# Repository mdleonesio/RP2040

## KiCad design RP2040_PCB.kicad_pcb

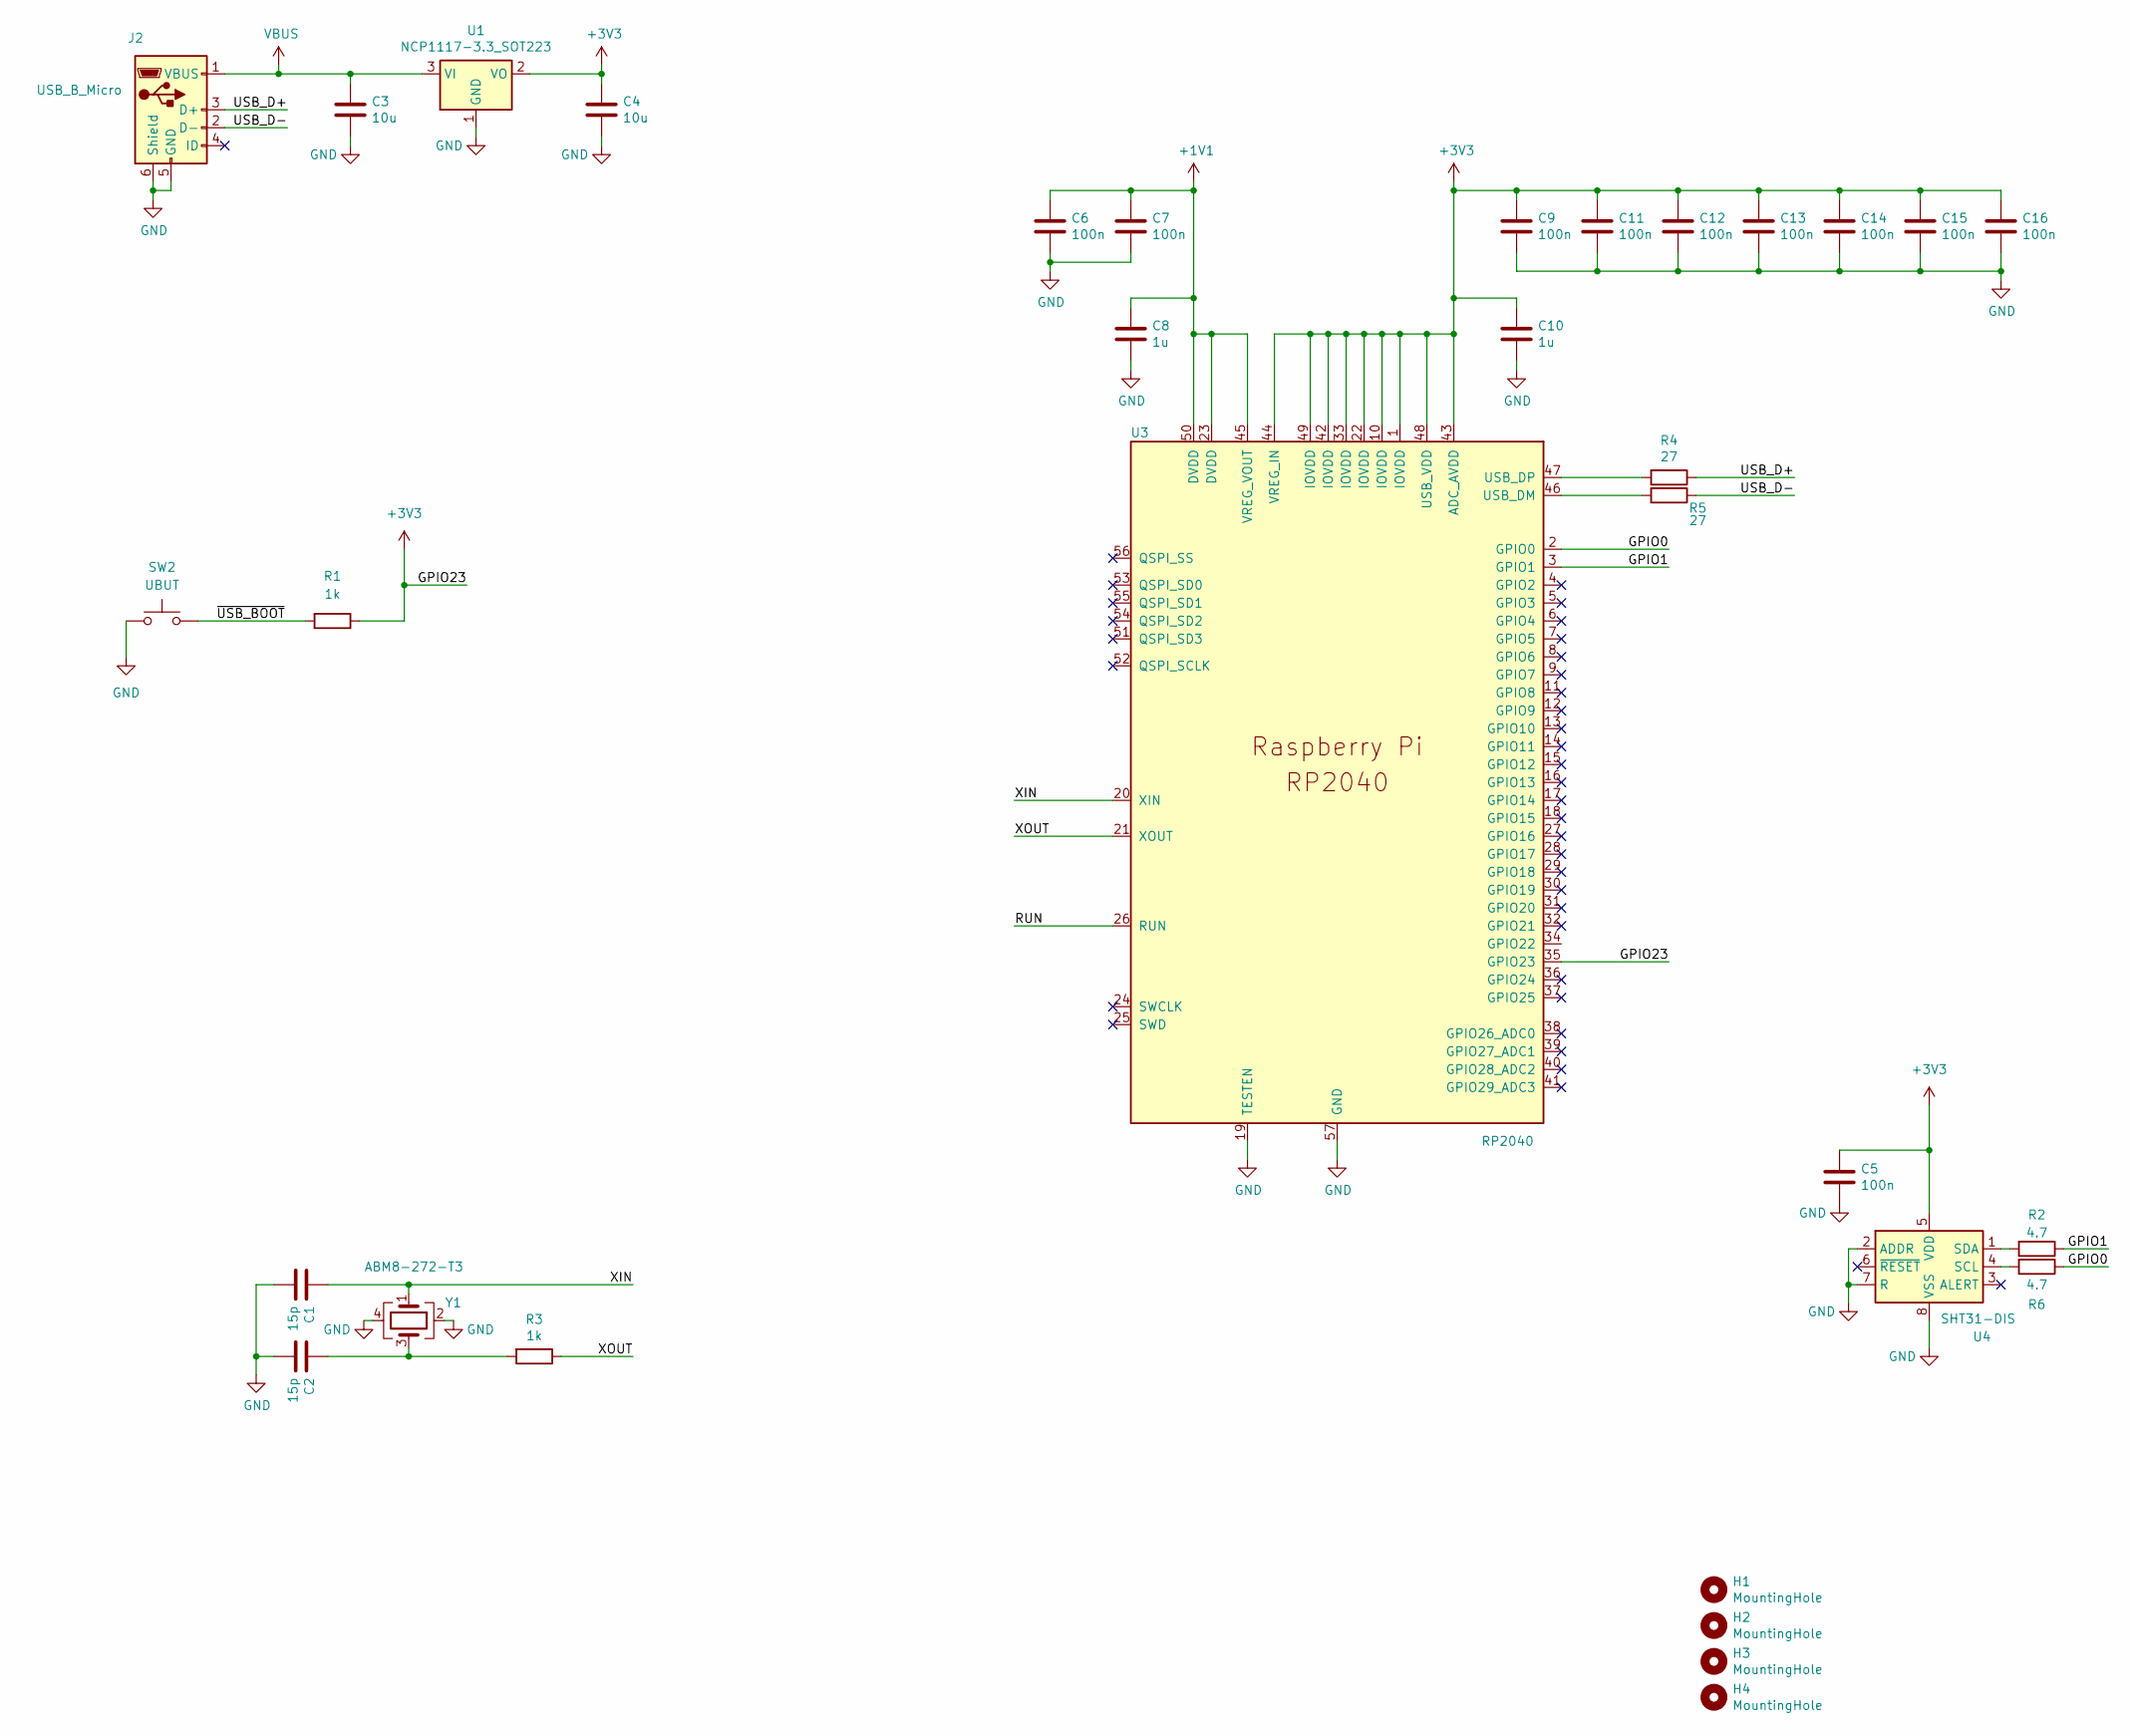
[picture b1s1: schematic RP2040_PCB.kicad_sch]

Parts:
C1, C2: 15p; C_0402_1005Metric
C3, C4: 10u; C_0805_2012Metric
C5, C6, C7, C9, C11, C12, C13, C14, C15, C16: 100n; C_0402_1005Metric
C8, C10: 1u; C_0402_1005Metric
H1, H2, H3, H4: MountingHole; MountingHole_2.7mm_M2.5
J2: USB_B_Micro; USB_Micro-B_Amphenol_10103594-0001LF_Horizontal_modified
R1, R3: 1k; R_0402_1005Metric
R2, R6: 4.7; R_0402_1005Metric
R4, R5: 27; R_0402_1005Metric
SW2: UBUT; SW_Push_1P1T_NO_6x6mm_H9.5mm
U1: NCP1117-3.3_SOT223; SOT-223-3_TabPin2
U3: RP2040; RP2040-QFN-56
U4: SHT31-DIS; Sensirion_DFN-8-1EP_2.5x2.5mm_P0.5mm_EP1.1x1.7mm
Y1: ABM8-272-T3; Crystal_SMD_3225-4Pin_3.2x2.5mm

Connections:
+1V1: C6.1, C7.1, C8.1, U3.23 (DVDD), U3.45 (VREG_VOUT), U3.50 (DVDD)
+3V3: C4.1, C5.1, C9.1, C10.1, C11.1, C12.1, C13.1, C14.1, C15.1, C16.1, R1.1, U1.2 (VO), U3.1 (IOVDD), U3.10 (IOVDD), U3.22 (IOVDD), U3.33 (IOVDD), U3.35 (GPIO23), U3.42 (IOVDD), U3.43 (ADC_AVDD), U3.44 (VREG_IN), U3.48 (USB_VDD), U3.49 (IOVDD), U4.5 (VDD)
/GPIO0: R6.1, U3.2 (GPIO0)
/GPIO1: R2.1, U3.3 (GPIO1)
/RUN: U3.26 (RUN)
/USB_D+: J2.3 (D+), R4.1
/USB_D-: J2.2 (D-), R5.1
/XIN: C1.1, U3.20 (XIN), Y1.1
/XOUT: R3.1, U3.21 (XOUT)
/~USB_BOOT: R1.2, SW2.2
GND: C1.2, C2.2, C3.2, C4.2, C5.2, C6.2, C7.2, C8.2, C9.2, C10.2, C11.2, C12.2, C13.2, C14.2, C15.2, C16.2, J2.5 (GND), J2.6 (Shield), SW2.1, U1.1 (GND), U3.19 (TESTEN), U3.57 (GND), U4.2 (ADDR), U4.7 (R), U4.8 (VSS), U4.9 (VSS), Y1.2, Y1.4
unnamed: C2.1, R3.2, Y1.3
unnamed: R5.2, U3.46 (USB_DM)
unnamed: R4.2, U3.47 (USB_DP)
unnamed: R6.2, U4.4 (SCL)
unnamed: R2.2, U4.1 (SDA)
VBUS: C3.1, J2.1 (VBUS), U1.3 (VI)

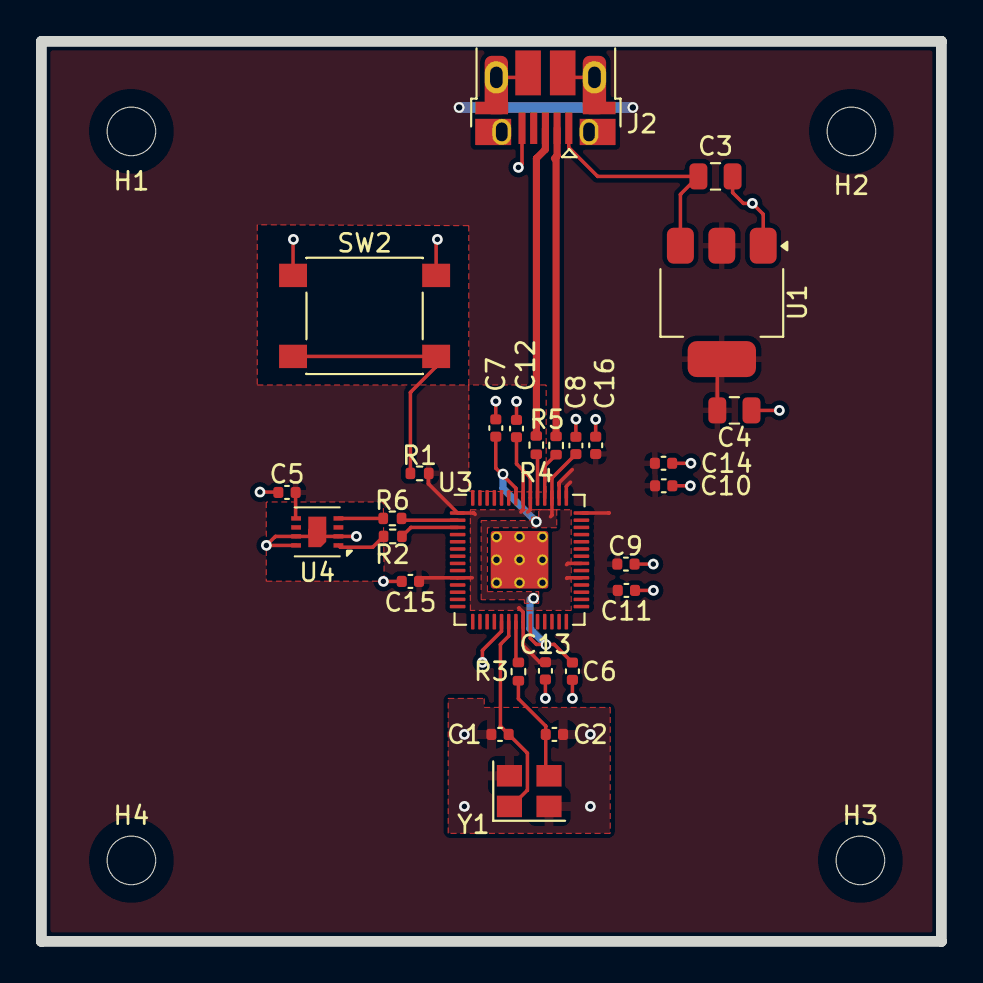
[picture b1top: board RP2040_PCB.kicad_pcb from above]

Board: 2 copper layers, 50.0 x 50.0 mm, 32 parts (0 on the bottom side), 16 nets.

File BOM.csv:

Designator,Footprint,Quantity,Value,
"C1, C2",402,2,15p,
"C10, C8",402,2,1u,
"C11, C12, C13, C14, C15, C16, C5, C6, C7, C9",402,10,100n,
"C3, C4",805,2,10u,
"H1, H2, H3, H4",MountingHole_2.7mm_M2.5,4,MountingHole,
J2,USB_Micro-B_Amphenol_10103594-0001LF_Horizontal_modified,1,USB_B_Micro,
"R1, R3",402,2,1k,
"R2, R6",402,2,4.7,
"R4, R5",402,2,27,
SW2,SW_Push_1P1T_NO_6x6mm_H9.5mm,1,UBUT,
U1,SOT-223-3_TabPin2,1,NCP1117-3.3_SOT223,
U3,RP2040-QFN-56,1,RP2040,
U4,Sensirion_DFN-8-1EP_2.5x2.5mm_P0.5mm_EP1.1x1.7mm,1,SHT31-DIS,
Y1,Crystal_SMD_3225-4Pin_3.2x2.5mm,1,ABM8-272-T3,

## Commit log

2024-09-18 RP2040 PCB Design
2024-09-18 BOM and POS
